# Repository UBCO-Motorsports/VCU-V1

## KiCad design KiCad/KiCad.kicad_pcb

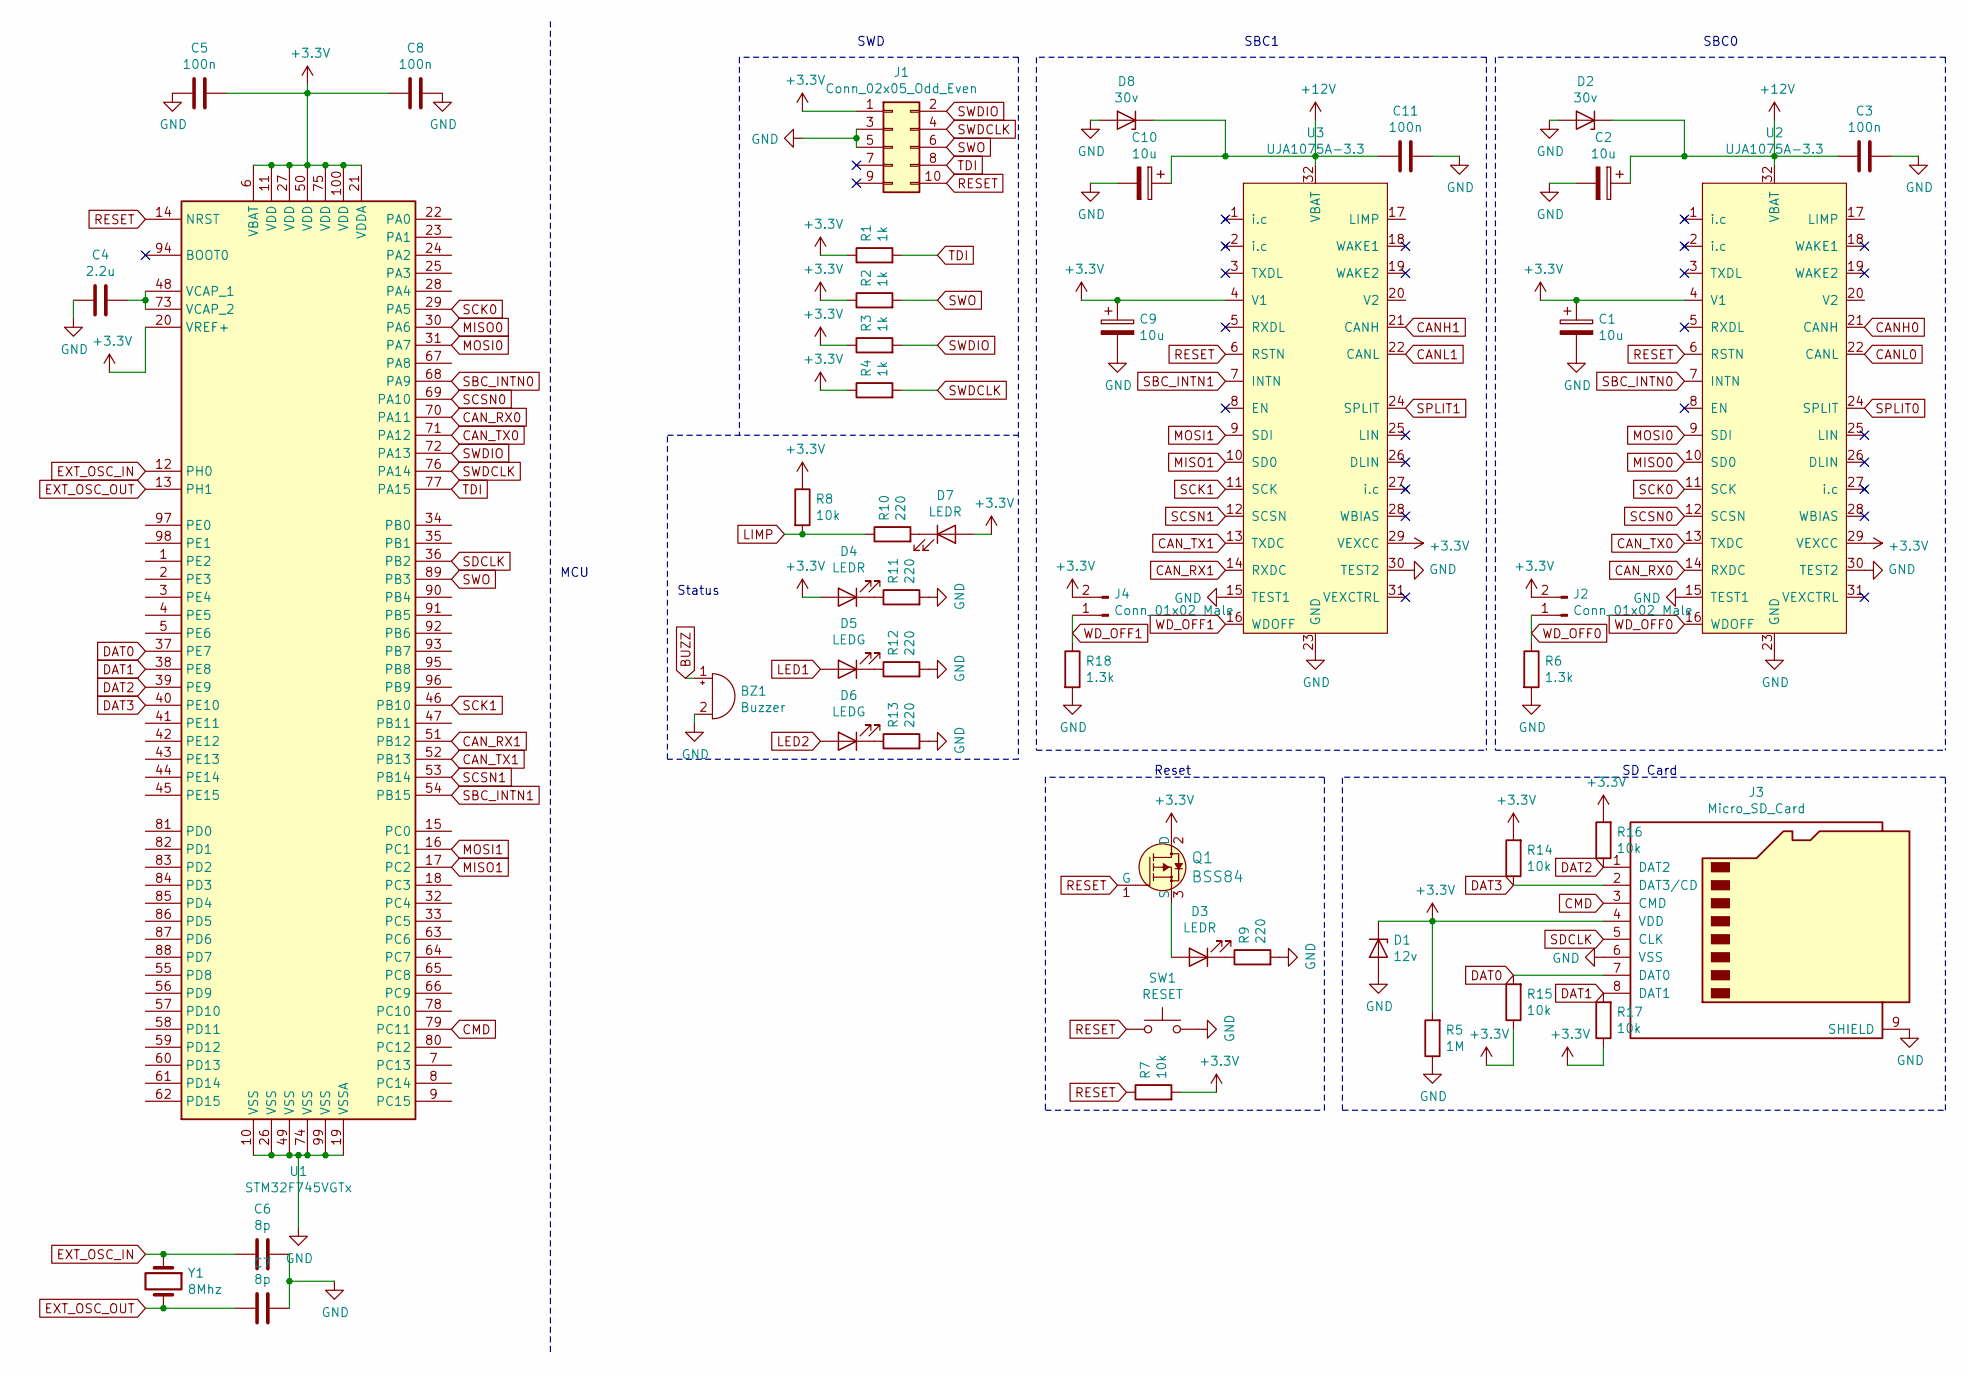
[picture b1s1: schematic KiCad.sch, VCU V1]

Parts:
BZ1: Buzzer; Buzzer_12x9.5RM7.6
C1, C2, C9, C10: 10u; C_0603_1608Metric_Pad1.05x0.95mm_HandSolder
C3, C5, C8, C11: 100n; C_0603_1608Metric_Pad1.05x0.95mm_HandSolder
C4: 2.2u; C_0603_1608Metric_Pad1.05x0.95mm_HandSolder
C6, C7: 8p; C_0603_1608Metric_Pad1.05x0.95mm_HandSolder
D1: 12v; SOT-23_Handsoldering
D2, D8: 30v; D_SOD-123
D3, D4, D7: LEDR; D_0603_1608Metric_Pad1.05x0.95mm_HandSolder
D5, D6: LEDG; D_0603_1608Metric_Pad1.05x0.95mm_HandSolder
J1: Conn_02x05_Odd_Even; PinHeader_2x05_P1.27mm_Vertical
J2, J4: Conn_01x02_Male; PinHeader_1x02_P1.27mm_Vertical
J3: Micro_SD_Card; microSD_HC_Wuerth_693072010801
Q1: BSS84; SOT-23-3; MPN BSS84; Digi-Key_PN BSS84CT-ND
R1, R2, R3, R4: 1k; R_0603_1608Metric_Pad1.05x0.95mm_HandSolder
R5: 1M; R_0603_1608Metric_Pad1.05x0.95mm_HandSolder
R6, R18: 1.3k; R_0603_1608Metric_Pad1.05x0.95mm_HandSolder
R7, R8, R14, R15, R16, R17: 10k; R_0603_1608Metric_Pad1.05x0.95mm_HandSolder
R9, R10, R11, R12, R13: 220; R_0603_1608Metric_Pad1.05x0.95mm_HandSolder
SW1: RESET; Crystal_SMD_0603-2Pin_6.0x3.5mm_HandSoldering
U1: STM32F745VGTx; LQFP-100_14x14mm_P0.5mm
U2, U3: UJA1075A-3.3; HTSSOP-38-1EP_6.1x12.5mm_P0.65mm_EP5.2x12.5mm_Mask3.39x6.35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
Y1: 8Mhz; Oscillator_SMD_Abracon_ASE-4Pin_3.2x2.5mm_HandSoldering

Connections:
+3V3: C1.1, C5.1, C8.2, C9.1, D1.1 (K), D4.2 (A), D7.2 (A), J1.1, J2.2, J3.4 (VDD), J4.2, Q1.2 (D), R1.1, R2.1, R3.1, R4.1, R5.2, R7.2, R8.1, R14.2, R15.1, R16.2, R17.1, U1.6 (VBAT), U1.11 (VDD), U1.20 (VREF+), U1.21 (VDDA), U1.27 (VDD), U1.50 (VDD), U1.75 (VDD), U1.100 (VDD), U2.4 (V1), U2.29 (VEXCC), U3.4 (V1), U3.29 (VEXCC)
+12V: C2.1, C3.2, C10.1, C11.2, D2.1 (K), D8.1 (K), U2.32 (VBAT), U3.32 (VBAT)
BUZZ: BZ1.1 (-)
CANH0: U2.21 (CANH)
CANH1: U3.21 (CANH)
CANL0: U2.22 (CANL)
CANL1: U3.22 (CANL)
CAN_RX0: U1.70 (PA11), U2.14 (RXDC)
CAN_RX1: U1.51 (PB12), U3.14 (RXDC)
CAN_TX0: U1.71 (PA12), U2.13 (TXDC)
CAN_TX1: U1.52 (PB13), U3.13 (TXDC)
CMD: J3.3 (CMD), U1.79 (PC11)
DAT0: J3.7 (DAT0), R15.2, U1.37 (PE7)
DAT1: J3.8 (DAT1), R17.2, U1.38 (PE8)
DAT2: J3.1 (DAT2), R16.1, U1.39 (PE9)
DAT3: J3.2 (DAT3/CD), R14.1, U1.40 (PE10)
EXT_OSC_IN: C6.2, U1.12 (PH0), Y1.1
EXT_OSC_OUT: C7.2, U1.13 (PH1), Y1.2
GND: BZ1.2 (+), C1.2, C2.2, C3.1, C4.2, C5.2, C6.1, C7.1, C8.1, C9.2, C10.2, C11.1, D1.2 (A), D2.2 (A), D8.2 (A), J1.3, J1.5, J3.6 (VSS), J3.9 (SHIELD), R5.1, R6.2, R9.2, R11.2, R12.2, R13.2, R18.2, SW1.2, U1.10 (VSS), U1.19 (VSSA), U1.26 (VSS), U1.49 (VSS), U1.74 (VSS), U1.99 (VSS), U2.15 (TEST1), U2.23 (GND), U2.30 (TEST2), U3.15 (TEST1), U3.23 (GND), U3.30 (TEST2)
LED1: D5.2 (A)
LED2: D6.2 (A)
LIMP: R8.2, R10.1
MISO0: U1.30 (PA6), U2.10 (SD0)
MISO1: U1.17 (PC2), U3.10 (SD0)
MOSI0: U1.31 (PA7), U2.9 (SDI)
MOSI1: U1.16 (PC1), U3.9 (SDI)
unnamed: C4.1, U1.48 (VCAP_1), U1.73 (VCAP_2)
unnamed: D3.1 (K), R9.1
unnamed: D3.2 (A), Q1.3 (S)
unnamed: D4.1 (K), R11.1
unnamed: D5.1 (K), R12.1
unnamed: D6.1 (K), R13.1
unnamed: D7.1 (K), R10.2
RESET: J1.10, Q1.1 (G), R7.1, SW1.1, U1.14 (NRST), U2.6 (RSTN), U3.6 (RSTN)
SBC_INTN0: U1.68 (PA9), U2.7 (INTN)
SBC_INTN1: U1.54 (PB15), U3.7 (INTN)
SCK0: U1.29 (PA5), U2.11 (SCK)
SCK1: U1.46 (PB10), U3.11 (SCK)
SCSN0: U1.69 (PA10), U2.12 (SCSN)
SCSN1: U1.53 (PB14), U3.12 (SCSN)
SDCLK: J3.5 (CLK), U1.36 (PB2)
SPLIT0: U2.24 (SPLIT)
SPLIT1: U3.24 (SPLIT)
SWDCLK: J1.4, R4.2, U1.76 (PA14)
SWDIO: J1.2, R3.2, U1.72 (PA13)
SWO: J1.6, R2.2, U1.89 (PB3)
TDI: J1.8, R1.2, U1.77 (PA15)
WD_OFF0: J2.1, R6.1, U2.16 (WDOFF)
WD_OFF1: J4.1, R18.1, U3.16 (WDOFF)

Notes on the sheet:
SBC0
SWD
SD Card
Reset
Status
MCU
SBC1

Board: 2 copper layers, 47 parts (0 on the bottom side), 39 nets, no tracks yet.

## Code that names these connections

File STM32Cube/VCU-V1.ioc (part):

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PA6.Mode=Full_Duplex_Master
PA7.Mode=Full_Duplex_Master
Mcu.UserName=STM32F745VGTx
PB10.Mode=Full_Duplex_Master
PC11.Signal=QUADSPI_BK2_NCS
PC2.Signal=SPI2_MISO
PE10.Mode=Single Bank 2
PA11.Mode=CAN_Activate
PC2.Mode=Full_Duplex_Master
PB13.Signal=CAN2_TX
PB15.Signal=GPIO_Output
PE8.Mode=Single Bank 2
PA13.Signal=SYS_JTMS-SWDIO
PA12.Signal=CAN1_TX
PH0/OSC_IN.Mode=HSE-External-Oscillator
PA9.Signal=GPIO_Output
PH1/OSC_OUT.Signal=RCC_OSC_OUT
PB10.Signal=SPI2_SCK
PB14.Signal=GPIO_Output
PA5.Signal=SPI1_SCK
RCC.HSE_VALUE=25000000
PB2.Signal=QUADSPI_CLK
PB3.Mode=JTAG_4_pins
board=custom
PA15.Mode=JTAG_4_pins
PH0/OSC_IN.Signal=RCC_OSC_IN
PE8.Signal=QUADSPI_BK2_IO1
PE9.Signal=QUADSPI_BK2_IO2
PA14.Mode=JTAG_4_pins
PA13.Mode=JTAG_4_pins
PH1/OSC_OUT.Mode=HSE-External-Oscillator
PE10.Signal=QUADSPI_BK2_IO3
Mcu.Name=STM32F745V(E-G)Tx
PB3.Signal=SYS_JTDO-SWO
Mcu.Package=LQFP100
PE7.Mode=Single Bank 2
PA6.Signal=SPI1_MISO
PB12.Mode=CAN_Activate
PA12.Mode=CAN_Activate
PB2.Mode=Single Bank 2
PA11.Signal=CAN1_RX
PA10.Signal=GPIO_Output
PA14.Signal=SYS_JTCK-SWCLK
PA15.Signal=SYS_JTDI
PE9.Mode=Single Bank 2
PC11.Mode=Single Bank 2
PB13.Mode=CAN_Activate
PE7.Signal=QUADSPI_BK2_IO0
PC1.Signal=SPI2_MOSI
PB12.Signal=CAN2_RX
PC1.Mode=Full_Duplex_Master
PA7.Signal=SPI1_MOSI
PA5.Mode=Full_Duplex_Master

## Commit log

2021-05-22 Started Designing Added some basic circuits
2021-05-23 SPI, reset, CAN and status
2021-05-29 Two SBCs and Autogenerated STM32cube code
